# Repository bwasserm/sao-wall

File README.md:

# SAO Wall

Mount your SAOs on your wall for display.

[Hackaday.io Page](https://hackaday.io/project/203082-sao-wall-tile)

## Design Goals
* Wall-mountable: that's the point
* USB-powered: Ubiquitous and easy to acquire
* Modular and Tileable: Easy to acquire arbitrary numbers to assemble and arrange however you want
* Chainable: Can be connected together to share a power source
* Simple: Can support SAOs that only require power without software
* Smart: Can support interacting with I2C and GPIO on smart SAOs
* Accessible: Keep component cost low and hand solderable for home assembly 

## Desgin trades/notes
* USB provides 5V 3A without a PD controller, which should be enough
* SAO [1.68bis](https://docs.google.com/document/u/0/d/1EJqvkkLMAPsQ9VWF5A4elWoi0qMlKyr5Giw5rqRmtnM/mobilebasic?pli=1) spec specifies 250mA max per SAO, but most are smaller, so a 500mA 3.3V regulator seems reasonable for 4 SAOs. However it can be easily swapped for another at lower or higher current.
* I tried board-edge connectors at first, but that really complicates making arbitrary layouts. Using cables makes that way easier, and USB-C connectors seem appropriate. Also, getting alignment correct of the connectors on the 60deg edges of the hexagon seemed more difficult.
* One in and two out connectors is enough to make a power binary tree. I don't have any current monitoring yet, so be careful how many boards and SAOs get connected to the same supply.
* 5cm per side is a nice round number, and keeps the tiles small, but big enough for the SAOs to have some space between them. Also, it should be plenty small enough for 0.3m USB cables between tiles, without being too tight or having too much extra slack to hide.
* The Raspberry Pi Pico W is optional, for talking to smart SAOs (I2C or GPIO) and controlling the 3.3V regulator to turn them on and off. A Pico 2 W should also work. I wanted this to be compatible with firmware similar to the 2024 Supercon badge.
* I picked Pico pins for 3 of the SAOs' GPIOs to be connected to UARTs on the Pico. It only has two UARTs, but at least those are options.
* I wanted to put a current shunt on the 3.3V regulator to measure the load of the SAOs, but I didn't want to have the voltage drop on that rail, or add the op-amp to measure the tiny voltage difference to do that properly. At least not on this rev, but maybe a future rev.
* No, its not going to be great RF performance from the Pico, but hopefully good enough.
* The tiles can be arranged or connected in any order. All smart behavior is localized to the one tile, so it doesn't matter where it gets connected in the chain.

## BOM
* 1x IC REG BUCK 3.3V 500MA TSOT23-5  MCP1603BT-330I/OS [Datasheet](https://ww1.microchip.com/downloads/aemDocuments/documents/OTH/ProductDocuments/DataSheets/22042B.pdf) [Digikey](https://www.digikey.com/en/products/detail/microchip-technology/MCP1603BT-330I-OS/22611630)
* 4x S9717-ND CONN HDR 6POS 0.1 GOLD PCB [Digikey](https://www.digikey.com/en/products/detail/sullins-connector-solutions/SFH11-NBPC-D03-ST-BK/4558818)
* 3x USB4125-GF-A CONN RCPT TYPE C 6P SMD RA [Datasheet](https://mm.digikey.com/Volume0/opasdata/d220001/medias/docus/6501/USB4125%20Product%20Spec.pdf) [Digikey](https://www.digikey.com/en/products/detail/gct/USB4125-GF-A/13547388)
* 2x 5.1k 0603 Resistor [Digikey](https://www.digikey.com/en/products/detail/yageo/RC0805JR-075K1L/728338)
* 2x 4.7uF+ Capacitor [Digikey](https://www.digikey.com/en/products/detail/samsung-electro-mechanics/CL21A106KOQNNNG/3894417)
* 1x 4.7uH Inductor [Digikey](https://www.digikey.com/en/products/detail/inpaq-technology-co-ltd/WIP252010S-4R7MLDG/20486610)
* 1x 1.4M Resistor [Digikey](https://www.digikey.com/en/products/detail/yageo/RC0805FR-071M4L/727488)

Digikey Shopping Cart: https://www.digikey.com/short/hjqzcd2n

Optional
* 1x Raspberry Pi Pico (2) W  [Pico W Datasheet](https://datasheets.raspberrypi.com/picow/pico-w-datasheet.pdf) [Pico 2 W Datasheet](https://datasheets.raspberrypi.com/picow/pico-2-w-datasheet.pdf)
* 2x 5.1k 0603 Resistors
* 1x Schottky 0603 Diode

# Renders

# Attribution and feedback
If you make and distribute this, please add a reference back to me or this repo so people can know where it came from. If you make any new designs to integrate into this system, please let me know so everyone can learn about them. Thanks!

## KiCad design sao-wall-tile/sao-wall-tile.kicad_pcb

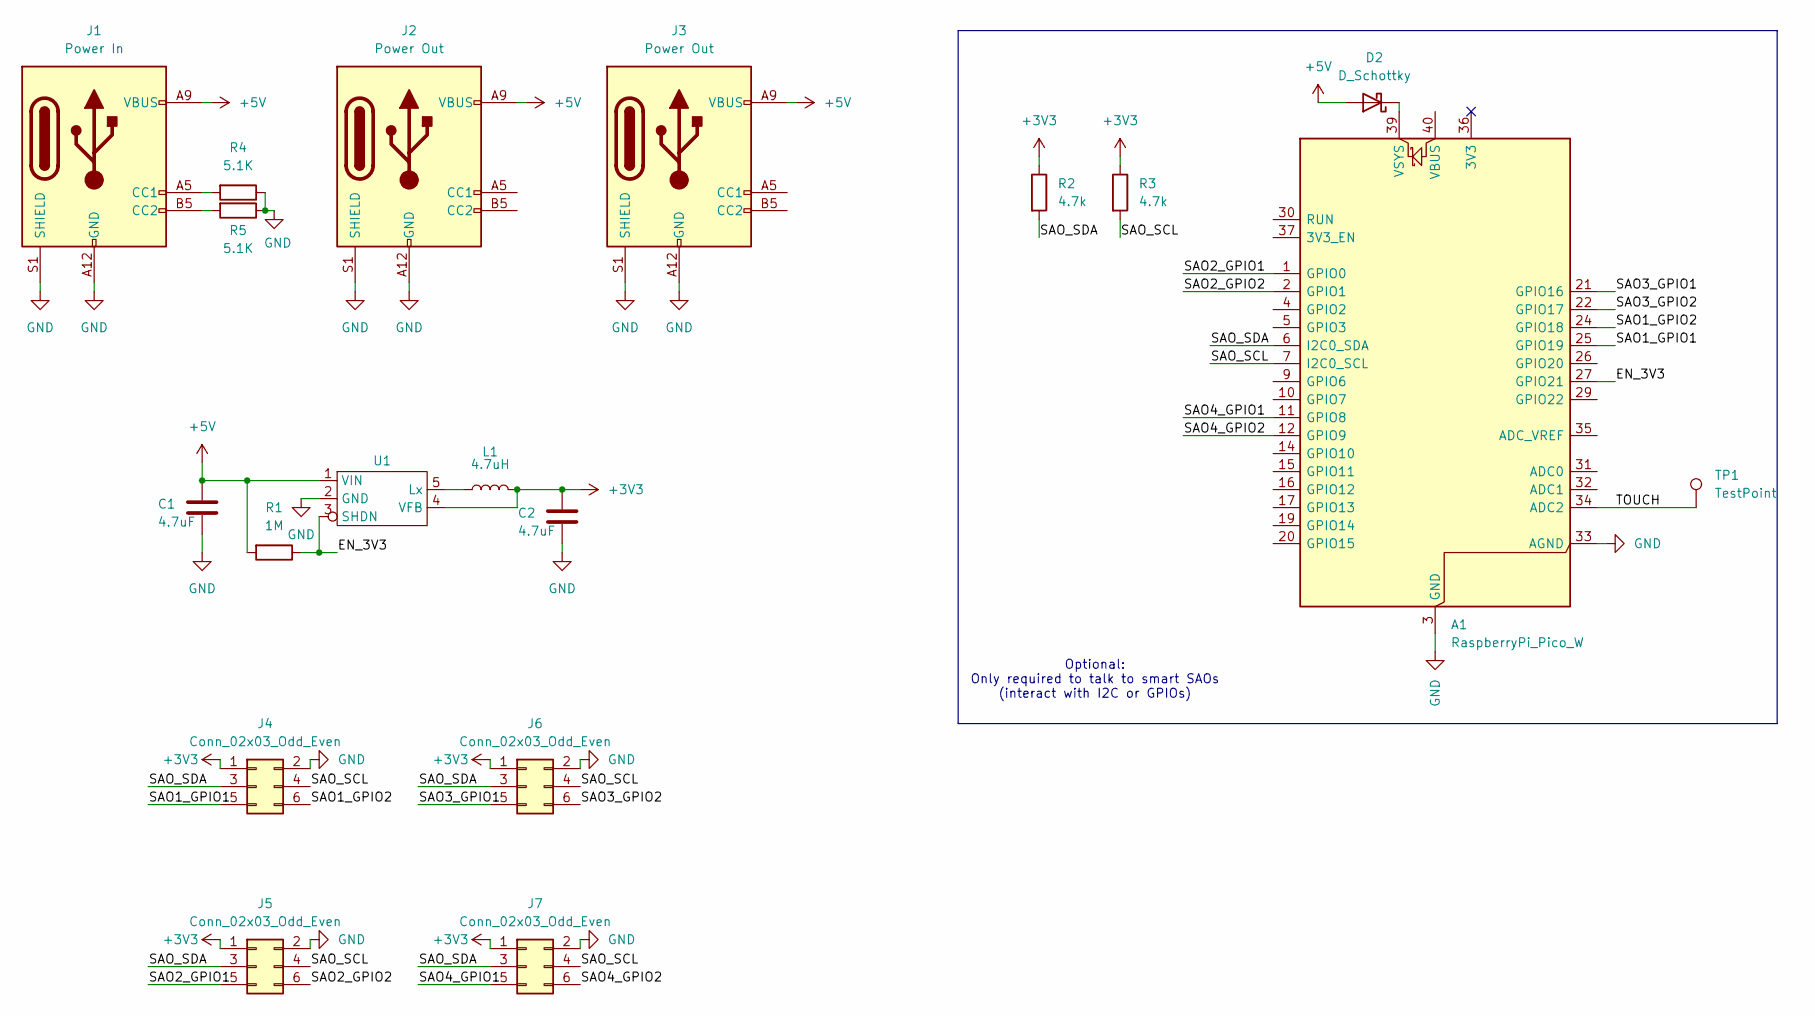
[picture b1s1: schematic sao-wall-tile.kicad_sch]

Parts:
A1: RaspberryPi_Pico_W; RaspberryPi_Pico_W_SMD_HandSolder
C1, C2: 4.7uF; C_0805_2012Metric_Pad1.18x1.45mm_HandSolder
D2: D_Schottky; D_0805_2012Metric_Pad1.15x1.40mm_HandSolder
J1: Power In; USB_C_Receptacle_GCT_USB4125-xx-x_6P_TopMnt_Horizontal
J2, J3: Power Out; USB_C_Receptacle_GCT_USB4125-xx-x_6P_TopMnt_Horizontal
J4, J5, J6, J7: Conn_02x03_Odd_Even; PinSocket_2x03_P2.54mm_Vertical
L1: 4.7uH; L_1008_2520Metric_Pad1.43x2.20mm_HandSolder
R1: 1M; R_0805_2012Metric_Pad1.20x1.40mm_HandSolder
R2, R3: 4.7k; R_0805_2012Metric_Pad1.20x1.40mm_HandSolder
R4, R5: 5.1K; R_0805_2012Metric_Pad1.20x1.40mm_HandSolder
TP1: TestPoint; TestPoint_Pad_D4.0mm
U1: TSOT-23-5_HandSoldering

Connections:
+3V3: C2.1, J4.1, J5.1, J6.1, J7.1, L1.2, R2.1, R3.1, U1.4 (VFB)
+5V: C1.1, D2.2 (A), J1.A9 (VBUS), J1.B9 (VBUS), J2.A9 (VBUS), J2.B9 (VBUS), J3.A9 (VBUS), J3.B9 (VBUS), R1.2, U1.1 (VIN)
/EN_3V3: A1.27 (GPIO21), R1.1, U1.3 (SHDN)
/SAO1_GPIO1: A1.25 (GPIO19), J4.5
/SAO1_GPIO2: A1.24 (GPIO18), J4.6
/SAO2_GPIO1: A1.1 (GPIO0), J5.5
/SAO2_GPIO2: A1.2 (GPIO1), J5.6
/SAO3_GPIO1: A1.21 (GPIO16), J6.5
/SAO3_GPIO2: A1.22 (GPIO17), J6.6
/SAO4_GPIO1: A1.11 (GPIO8), J7.5
/SAO4_GPIO2: A1.12 (GPIO9), J7.6
/SAO_SCL: A1.7 (I2C0_SCL), J4.4, J5.4, J6.4, J7.4, R3.2
/SAO_SDA: A1.6 (I2C0_SDA), J4.3, J5.3, J6.3, J7.3, R2.2
/TOUCH: A1.34 (ADC2), TP1.1
GND: A1.3 (GND), A1.8 (GND), A1.13 (GND), A1.18 (GND), A1.23 (GND), A1.28 (GND), A1.33 (AGND), A1.38 (GND), C1.2, C2.2, J1.A12 (GND), J1.B12 (GND), J1.S1 (SHIELD), J2.A12 (GND), J2.B12 (GND), J2.S1 (SHIELD), J3.A12 (GND), J3.B12 (GND), J3.S1 (SHIELD), J4.2, J5.2, J6.2, J7.2, R4.1, R5.1, U1.2 (GND)
unnamed: A1.39 (VSYS), D2.1 (K)
unnamed: J1.A5 (CC1), R4.2
unnamed: J1.B5 (CC2), R5.2
unnamed: L1.1, U1.5 (Lx)

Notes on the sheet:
Optional: Only required to talk to smart SAOs (interact with I2C or GPIOs)

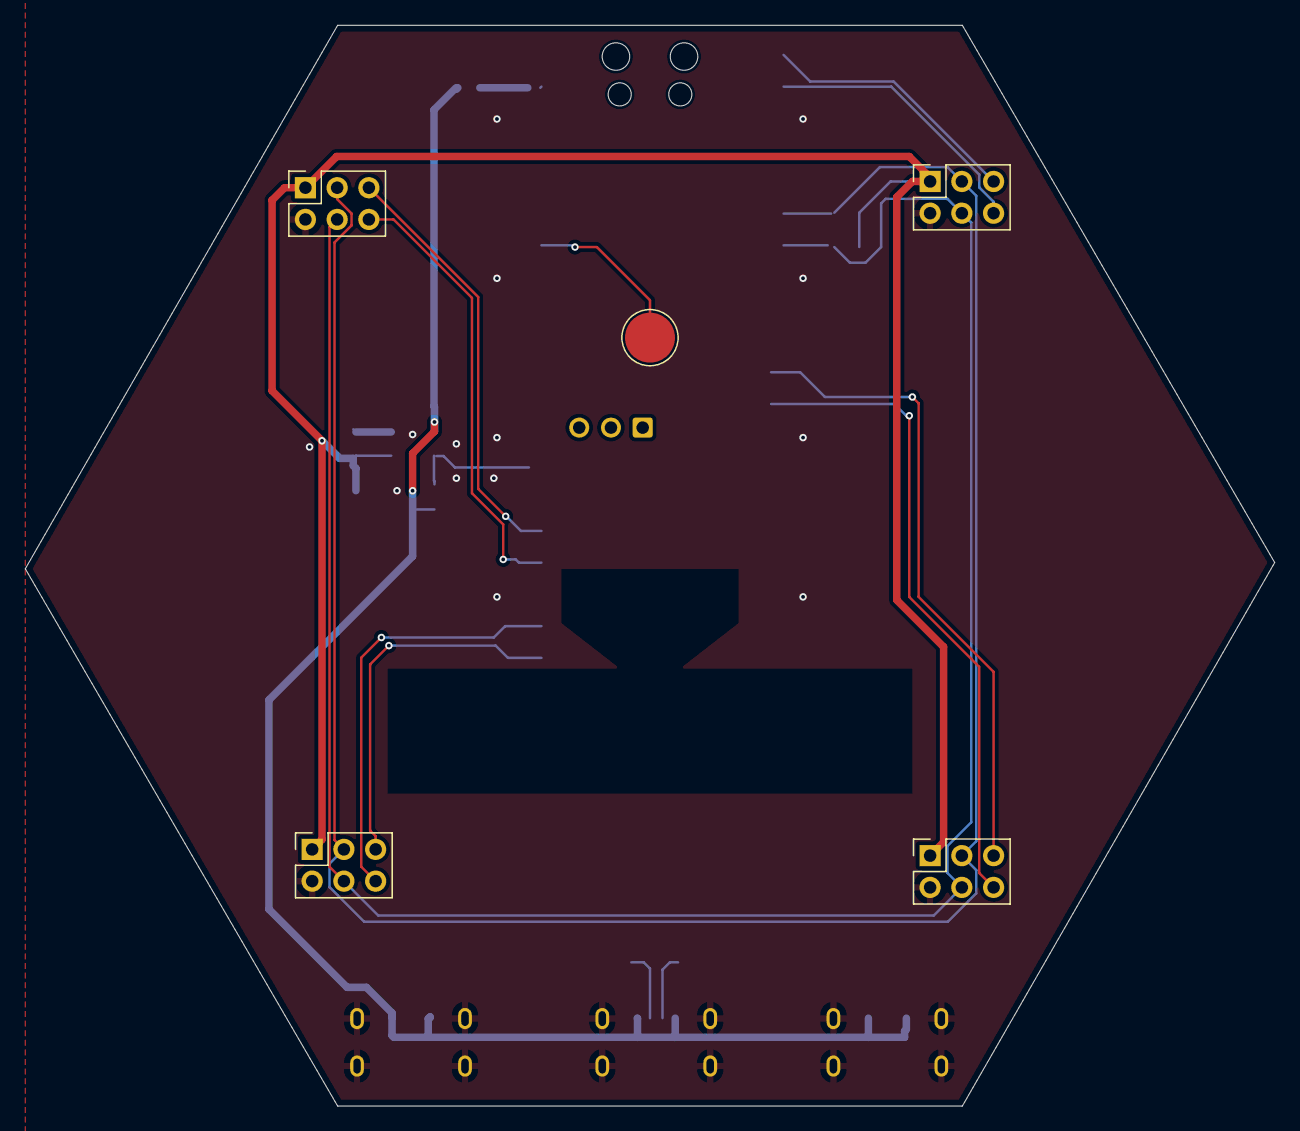
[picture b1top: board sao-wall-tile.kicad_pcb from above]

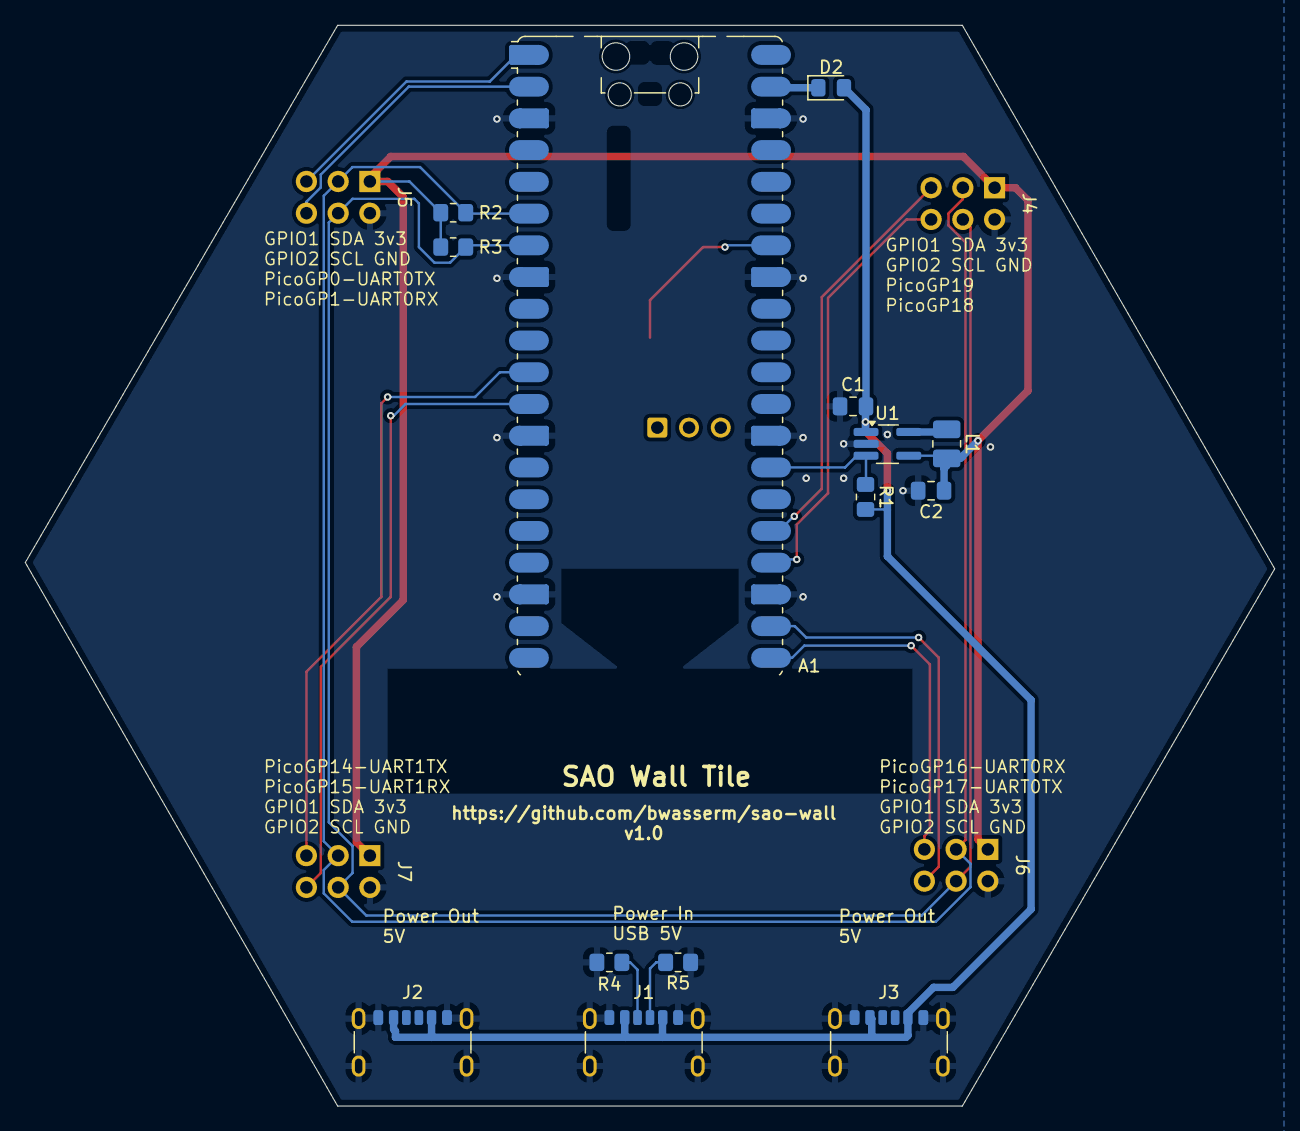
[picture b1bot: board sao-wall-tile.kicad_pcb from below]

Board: 2 copper layers, 100.0 x 86.5 mm, 19 parts (14 on the bottom side), 19 nets.

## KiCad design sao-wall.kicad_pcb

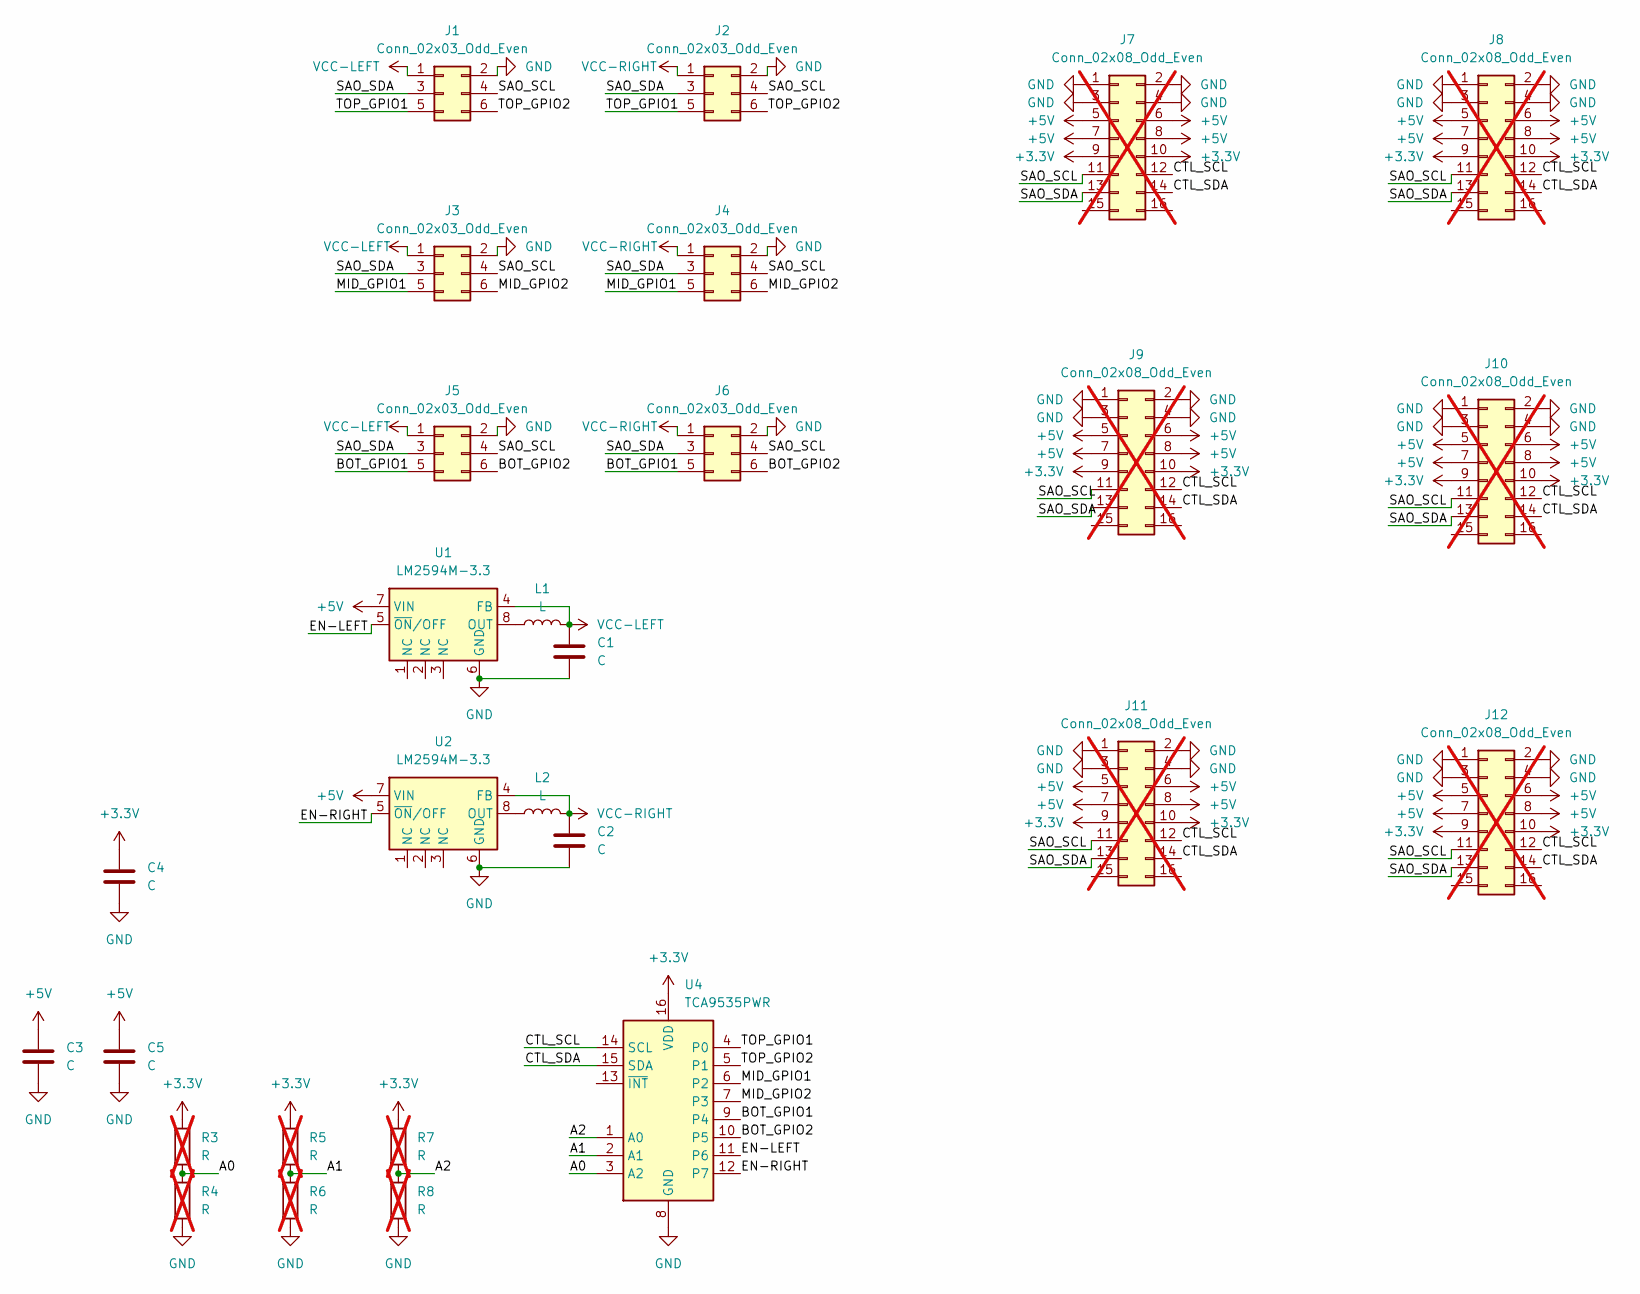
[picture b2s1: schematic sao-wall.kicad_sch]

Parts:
C1, C2, C3, C4, C5: C; C_0603_1608Metric
J1, J2, J3, J4, J5, J6: Conn_02x03_Odd_Even; PinSocket_2x03_P2.54mm_Vertical
J7, J8, J9, J10, J11, J12: Conn_02x08_Odd_Even; PinHeader_2x08_P2.00mm_Vertical; not fitted
L1, L2: L; L_0603_1608Metric
R3, R4, R5, R6, R7, R8: R; R_0603_1608Metric; not fitted
U1, U2: LM2594M-3.3; SOIC-8_3.9x4.9mm_P1.27mm
U4: TCA9535PWR; TSSOP-24_4.4x7.8mm_P0.65mm

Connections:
+3.3V: C4.1, J7.9, J7.10, J8.9, J8.10, J9.9, J9.10, J10.9, J10.10, J11.9, J11.10, J12.9, J12.10, R3.1, R5.1, R7.1, U4.16 (VDD)
+5V: C3.1, C5.1, J7.5, J7.6, J7.7, J7.8, J8.5, J8.6, J8.7, J8.8, J9.5, J9.6, J9.7, J9.8, J10.5, J10.6, J10.7, J10.8, J11.5, J11.6, J11.7, J11.8, J12.5, J12.6, J12.7, J12.8, U1.7 (VIN), U2.7 (VIN)
/A0: R3.2, R4.1, U4.3 (A2)
/A1: R5.2, R6.1, U4.2 (A1)
/A2: R7.2, R8.1, U4.1 (A0)
/BOT_GPIO1: J5.5, J6.5, U4.9 (P4)
/BOT_GPIO2: J5.6, J6.6, U4.10 (P5)
/CTL_SCL: J7.12, J8.12, J9.12, J10.12, J11.12, J12.12, U4.14 (SCL)
/CTL_SDA: J7.14, J8.14, J9.14, J10.14, J11.14, J12.14, U4.15 (SDA)
/EN-LEFT: U1.5 (~ON/OFF), U4.11 (P6)
/EN-RIGHT: U2.5 (~ON/OFF), U4.12 (P7)
/MID_GPIO1: J3.5, J4.5, U4.6 (P2)
/MID_GPIO2: J3.6, J4.6, U4.7 (P3)
/SAO_SCL: J1.4, J2.4, J3.4, J4.4, J5.4, J6.4, J7.11, J8.11, J9.11, J10.11, J11.11, J12.11
/SAO_SDA: J1.3, J2.3, J3.3, J4.3, J5.3, J6.3, J7.13, J8.13, J9.13, J10.13, J11.13, J12.13
/TOP_GPIO1: J1.5, J2.5, U4.4 (P0)
/TOP_GPIO2: J1.6, J2.6, U4.5 (P1)
GND: C1.2, C2.2, C3.2, C4.2, C5.2, J1.2, J2.2, J3.2, J4.2, J5.2, J6.2, J7.1, J7.2, J7.3, J7.4, J8.1, J8.2, J8.3, J8.4, J9.1, J9.2, J9.3, J9.4, J10.1, J10.2, J10.3, J10.4, J11.1, J11.2, J11.3, J11.4, J12.1, J12.2, J12.3, J12.4, R4.2, R6.2, R8.2, U1.6 (GND), U2.6 (GND), U4.8 (GND)
unnamed: L1.1, U1.8 (OUT)
unnamed: L2.1, U2.8 (OUT)
VCC-LEFT: C1.1, J1.1, J3.1, J5.1, L1.2, U1.4 (FB)
VCC-RIGHT: C2.1, J2.1, J4.1, J6.1, L2.2, U2.4 (FB)

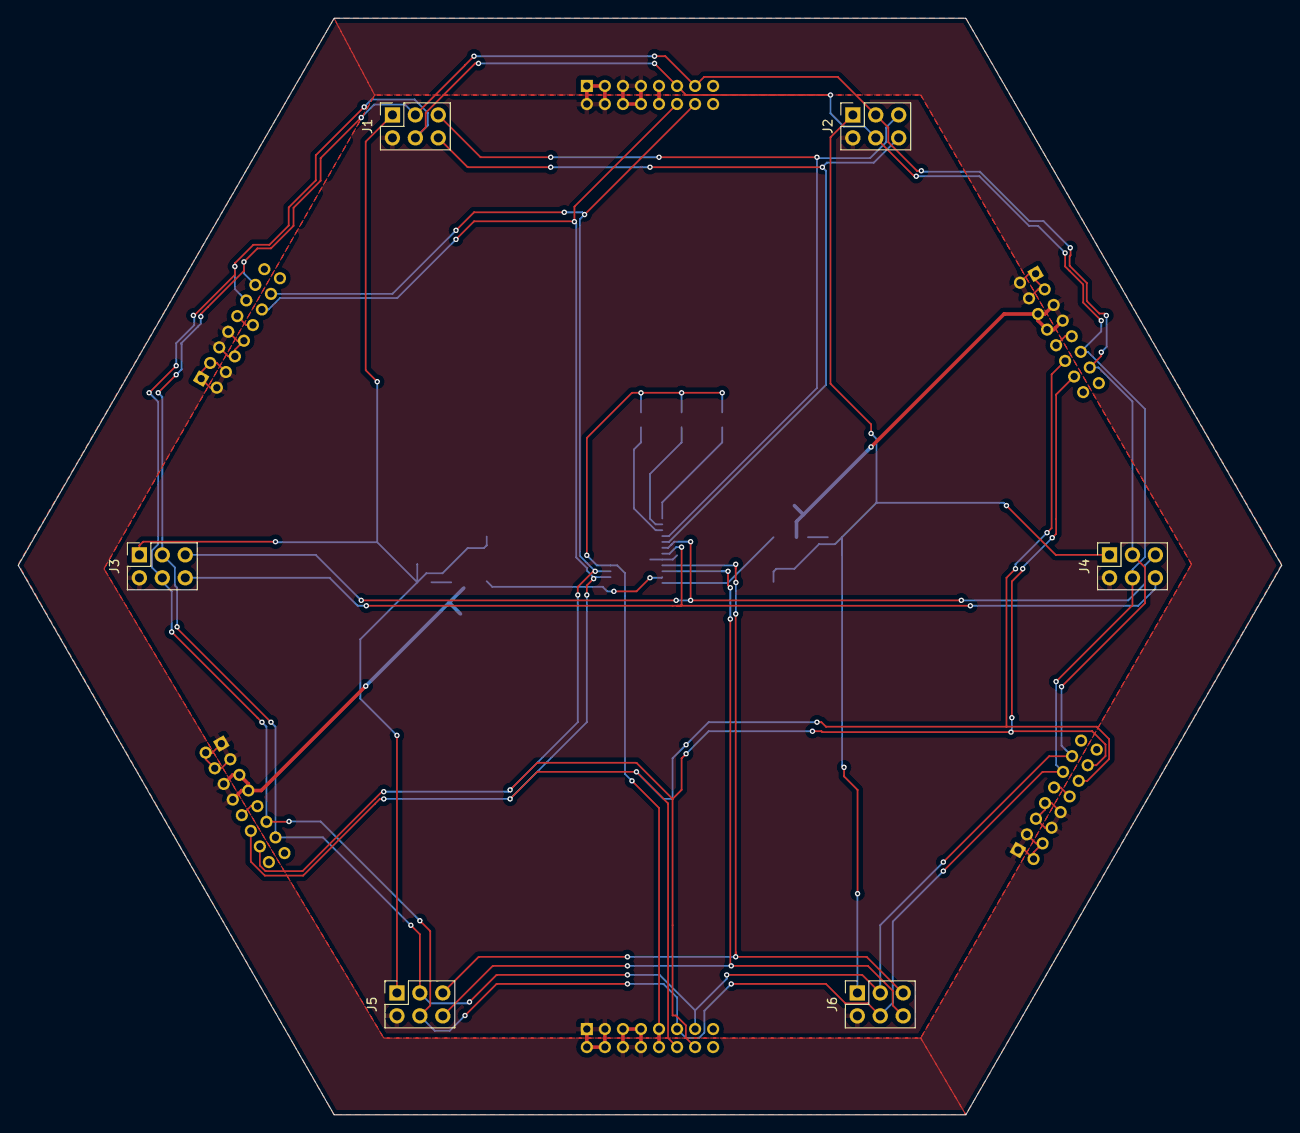
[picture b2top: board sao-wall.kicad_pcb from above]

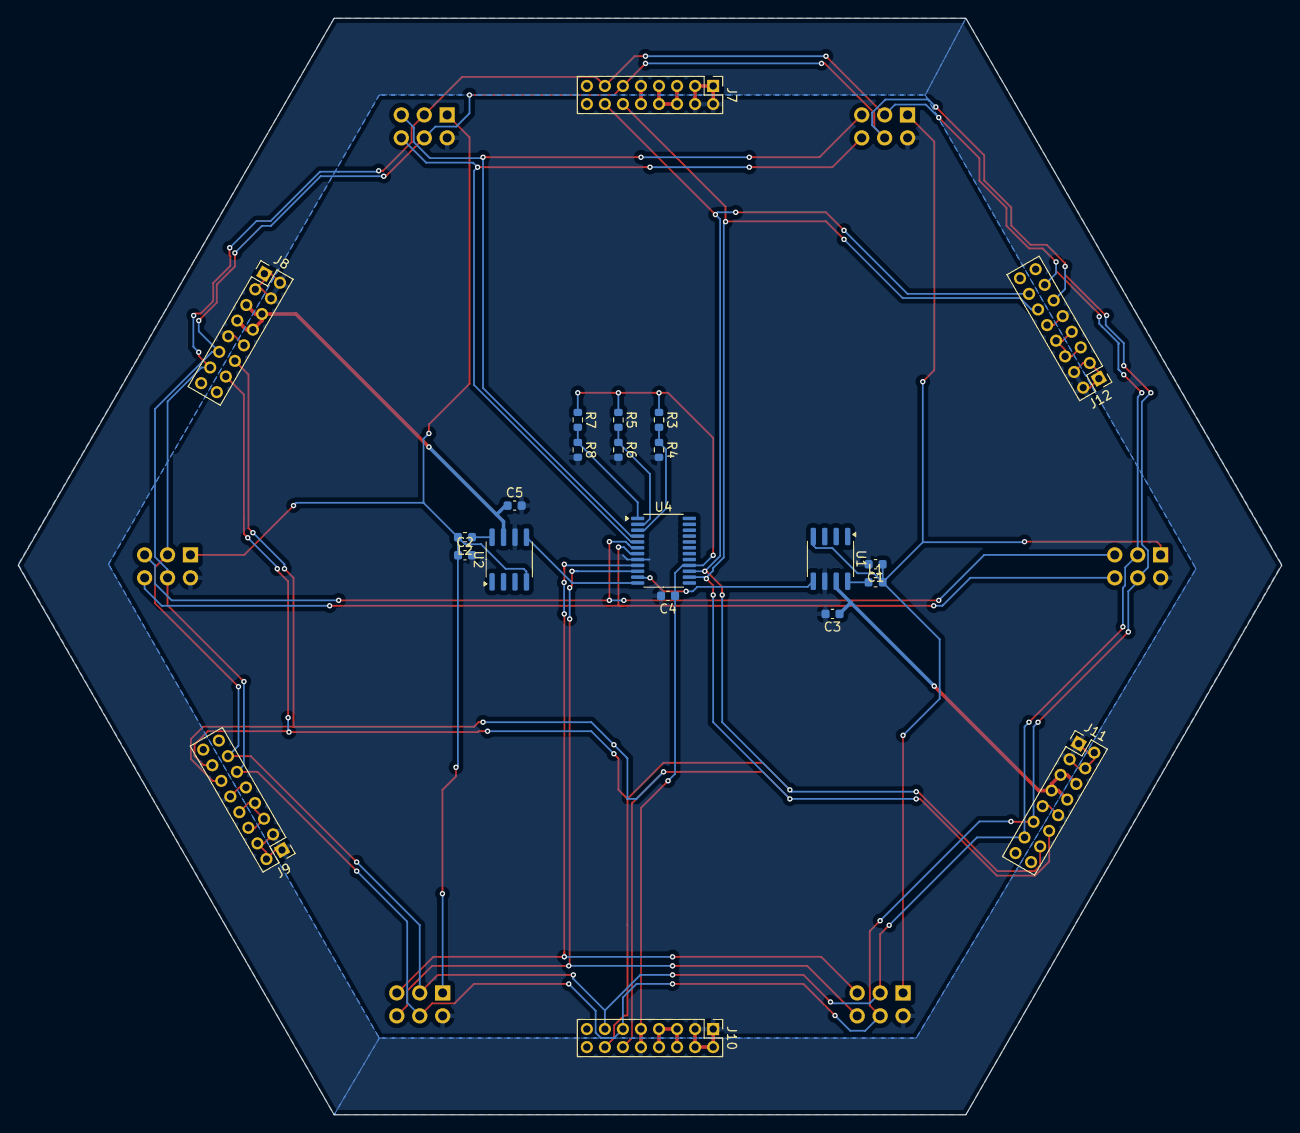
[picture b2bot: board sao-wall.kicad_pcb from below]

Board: 2 copper layers, 140.0 x 121.5 mm, 28 parts (22 on the bottom side), 22 nets.

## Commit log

2024-11-08 Create sao wall tile first draft
2024-11-24 Make tile larger, still needs routing
2024-11-24 Routed traces
2024-11-24 Small adjustments for pours
2025-03-27 Add new wall tile design
2025-03-29 Remove old concept
2025-03-30 Add README, clean up schematic and layout
2025-04-13 Update from review feedback
2025-04-13 Updates from picking components on digikey
2025-04-13 Made C2 smaller
2025-04-13 Updated digikey cart link
2025-04-14 Different buck converter for smaller and cheaper components
2025-04-14 Move GPIO pins, update from more review, enhance labels, update renders
2025-05-03 Exported schematic to pdf, saving frame before I remake it.
2025-05-04 Saving second rev
2025-05-04 Rebuilt frame, slightly better
2025-05-11 Larger and better, but need to go outer side back up to 110mm
2025-05-17 Larger 110mm sides, seems like the right size. Need to add extra cable slots.
2025-05-20 Add hackaday.io link to readme, add clip and frame stls
2025-06-01 Add cable hooks in frame
2025-07-18 Create LICENSE
2025-07-18 Update README.md
    Add attribution note in readme
